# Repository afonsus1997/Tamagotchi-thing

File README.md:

# Tamagotchi Thing

Just a dumb attempt to make a tamagotch.

Based on the amazing work of [jcrona](https://github.com/jcrona)!

#### Credits

3D models:
 - Kailh buttons by Manh Le

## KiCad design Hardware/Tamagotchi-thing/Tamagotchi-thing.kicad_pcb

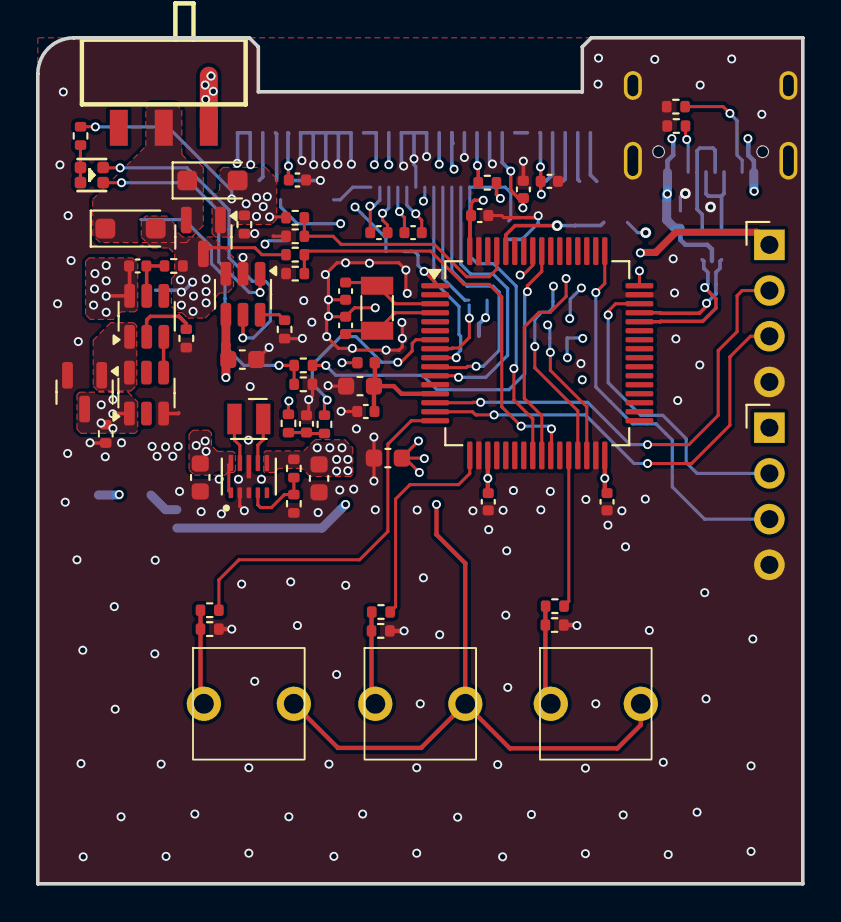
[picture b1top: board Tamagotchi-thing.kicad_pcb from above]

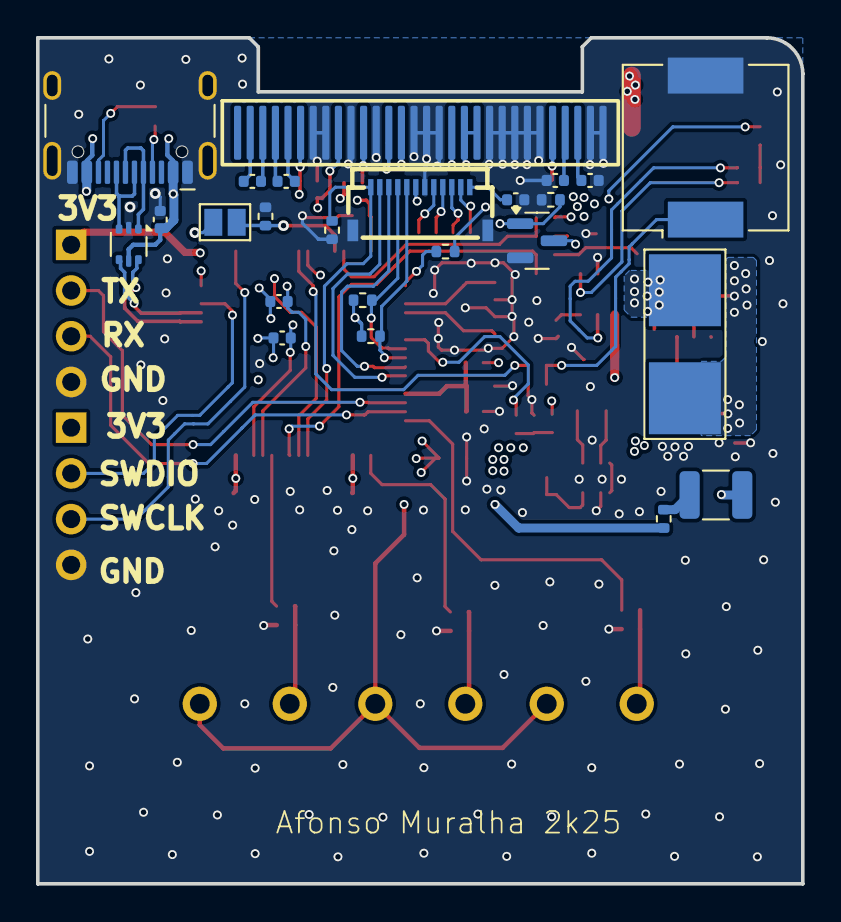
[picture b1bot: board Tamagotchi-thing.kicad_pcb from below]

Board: 4 copper layers, 42.5 x 47.0 mm, 86 parts (24 on the bottom side), 69 nets.

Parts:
BT1: Battery; Battery_Pads_4x4
C4, C5, C6: 1uF; C_0402_1005Metric
C7, C9, C10, C11, C12: 2.2uF; C_0402_1005Metric
C8: 4.7uF; C_0402_1005Metric
C13, C14: 12pF; C_0402_1005Metric
C15, C19, C20, C21, C24, C28: 100nF; C_0402_1005Metric
C18: 10nF; C_0603_1608Metric
C22: 1uF; C_0603_1608Metric
C23: 10nF; C_0402_1005Metric
C25, C27: 10uF; C_0603_1608Metric
C26: 22uF; C_0603_1608Metric
D1, D2: D_Schottky; D_SOD-123F
D3: LED_Dual_KKA; LED-SMD_4P-L1.6-W1.5-TL-1
J1: Conn_01x14; R_1210_3225Metric
J3: Conn_01x30; FFC-SMD_12P-P0.50_FH34SRJ-12S-0.5SH
J5: Conn_01x30; sh1106-1.3inch-oled_1
J6: USB_C_Receptacle_USB2.0; USB_C_Receptacle_HCTL_HC-TYPE-C-16P-01A
J7, J8: Conn_01x04; PinHeader_1x04_P2.54mm_Horizontal
JP1: SolderJumper_2_Open; SolderJumper-2_P1.3mm_Open_Pad1.0x1.5mm
L1: 39nH; L_0402_1005Metric
L2: 0.47uH; L_Wurth_WE-LQSH-2010
LS1: Speaker_Crystal; Buzzer_CUI_CPT-9019S-SMT
Q1: BSS138; SOT-23
Q3, Q4: AO3401A; SOT-23
Q5: FS8205A; SOT-23-6
R1: 15; R_0402_1005Metric
R2, R3, R4: 10k; R_0402_1005Metric
R6, R7, R11, R15, R16, R17, R18, R19, R22, R28, R32, R33: 100k; R_0402_1005Metric
R8, R9: 4.7k; C_0402_1005Metric
R10: 390k; C_0402_1005Metric
R12, R21, R27, R31: 330; R_0402_1005Metric
R13, R14: 5.1k; R_0402_1005Metric
R20, R34: 0; R_0402_1005Metric
R25, R35: 100; R_0402_1005Metric
R26, R36: 1k; R_0402_1005Metric
R37: 511k; R_0402_1005Metric
R38: 91k; R_0402_1005Metric
R39: 2k; R_0402_1005Metric
R42: 1.6k; R_0402_1005Metric
SW2, SW4, SW5: SW_Push; Kailh_mouse_button
SW6: SW_SPDT_321; SW-SMD_SK-3245S-L1-A-1
U1: USBLC6-2P6; SOT-666
U2: STM32L073RBTx; LQFP-64_10x10mm_P0.5mm
U3: DW01A; SOT-23-6
U4: TPS63802DLAR; VREG_TPS63802DLAR
U5: TP4057; TSOT-23-6
Y1: 32768Hz - 12,5 pF; Crystal_SMD_3215-2Pin_3.2x1.5mm

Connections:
3V3: C7.2, C10.2, C18.1, C19.1, C20.1, C21.1, C26.1, J3.7, J5.6, J5.9, J5.13, J7.1, J8.1, JP1.1 (A), L1.1, R1.2, R3.1, R4.1, R7.2, R8.2, R9.2, R11.1, R20.1, R37.1, SW2.2, SW4.2, SW5.2, U2.19 (VDD), U2.32 (VDD), U2.48 (VDD_USB), U2.64 (VDD), U4.6 (VOUT)
3V3A: C22.1, C23.1, L1.2, U2.13 (VDDA)
/MCU/BOOT0: JP1.2 (B), R15.1, U2.60 (BOOT0)
/MCU/LCD2.SCL: J3.9, R4.2, U2.8 (I2C3_SCL)
/MCU/LCD2.SDA: J3.8, R3.2, U2.9 (I2C3_SDA)
/MCU/LCD2_A0: J3.10, U2.10 (PC2)
/MCU/LCD2_BL_EN: Q1.1 (G), R2.1, U2.57 (TIM3_CH2)
/MCU/LCD2_CS: J3.12, R6.1, U2.24 (PC4)
/MCU/LCD2_RES: J3.11, U2.11 (PC3)
/MCU/OLED.SCL: J5.18, R8.1, U2.29 (I2C2_SCL)
/MCU/OLED.SDA: J5.19, J5.20, R9.1, U2.30 (I2C2_SDA)
/MCU/OLED_RST: J5.14, U2.25 (PC5)
/MCU/OSC_32_IN: C13.1, U2.3 (RCC_OSC32_IN), Y1.1
/MCU/OSC_32_OUT: C14.1, U2.4 (RCC_OSC32_OUT), Y1.2
/MCU/RST: R12.2, U2.7 (NRST)
/MCU/SPK: R25.2, U2.56 (TIM3_CH1)
/MCU/SWCLK: J7.3, U2.49 (SYS_SWCLK)
/MCU/SWDIO: J7.2, U2.46 (SYS_SWDIO)
/MCU/SW_CENTER: R27.1, U2.17 (PA3)
/MCU/SW_LEFT: R21.1, U2.16 (PA2)
/MCU/SW_RIGHT: R31.1, U2.28 (PB2)
/MCU/UART_RX: J8.3, U2.15 (USART4_RX)
/MCU/UART_TX: J8.2, U2.14 (USART4_TX)
/MCU/USB_D_N: U1.6 (I/O1), U2.44 (USB_DM)
/MCU/USB_D_P: U1.4 (I/O2), U2.45 (USB_DP)
/MCU/USB_D_RAW_N: J6.A7 (D-), J6.B7 (D-), U1.1 (I/O1)
/MCU/USB_D_RAW_P: J6.A6 (D+), J6.B6 (D+), U1.3 (I/O2)
/MCU/VBAT_SENSE: R18.2, R19.1, U2.26 (ADC_IN8)
/MCU/VBUS_SENSE: R16.2, R17.1, U2.61 (PB8)
/OLED/BS1: J5.11, R7.1
GND: C4.2, C7.1, C8.1, C10.1, C11.1, C13.2, C14.2, C15.2, C18.2, C19.2, C20.2, C21.2, C22.2, C23.2, C25.2, C26.2, C27.2, C28.2, J3.6, J3.MP (MountPin), J5.7, J5.8, J5.10, J5.12, J5.15, J5.16, J5.17, J5.21, J5.22, J5.23, J5.24, J5.25, J5.29, J5.30, J6.A1 (GND), J6.A12 (GND), J6.B1 (GND), J6.B12 (GND), J6.S1 (SHIELD), J7.4, J8.4, LS1.2, Q1.2 (S), Q4.2 (S), Q5.3 (S2), R2.2, R6.2, R10.1, R13.2, R14.2, R15.2, R17.2, R19.2, R22.2, R26.2, R28.2, R32.2, R33.2, R34.2, R36.2, R38.2, R42.2, U1.2 (GND), U2.12 (VSSA), U2.18 (VSS), U2.31 (VSS), U2.47 (VSS), U2.63 (VSS), U4.2 (MODE), U4.3 (AGND), U4.8 (GND), U5.2 (GND)
GND_BAT: BT1.2 (-), C24.2, Q4.3 (D), Q5.1 (D1), R34.1, U3.6 (GND)
unnamed: C15.1, R11.2, R12.1
unnamed: D1.1 (K), D2.1 (K), Q3.2 (S), SW6.2 (B)
unnamed: D3.3 (A2), D3.4 (A1), R39.2
unnamed: D3.1 (K1), U5.1 (~CHRG)
unnamed: D3.2 (K2), U5.5 (STDBY)
unnamed: J1.1, R1.1
unnamed: J1.2, Q1.3 (D)
unnamed: C4.1, J3.1
unnamed: C5.1, J3.2
unnamed: C5.2, J3.3
unnamed: C6.1, J3.4
unnamed: C6.2, J3.5
unnamed: C12.2, J5.2
unnamed: C12.1, J5.3
unnamed: C9.2, J5.4
unnamed: C9.1, J5.5
unnamed: J5.26, R10.2
unnamed: C8.2, J5.27
unnamed: C11.2, J5.28
unnamed: J6.A5 (CC1), R14.1
unnamed: J6.B5 (CC2), R13.1
unnamed: LS1.1, R25.1, R26.1
unnamed: Q4.1 (G), Q5.6 (G1), U3.1 (OD)
unnamed: Q5.4 (G2), U3.3 (OC)
unnamed: R21.2, R22.1, SW2.1
unnamed: R27.2, R28.1, SW4.1
unnamed: R31.2, R32.1, SW5.1
unnamed: C25.1, SW6.3 (A), U4.1 (EN), U4.10 (VIN)
unnamed: R20.2, U2.1 (VLCD)
unnamed: R36.1, U3.2 (CS)
unnamed: C24.1, R35.2, U3.5 (VCC)
unnamed: R37.2, R38.1, U4.4 (FB)
unnamed: L2.1, U4.9 (L1)
unnamed: L2.2, U4.7 (L2)
unnamed: R42.1, U5.6 (PROG)
VBAT: BT1.1 (+), D2.2 (A), Q3.3 (D), R18.1, R35.1, U5.3 (BAT)
VBUS: C27.1, C28.1, D1.2 (A), J6.A4 (VBUS), J6.A9 (VBUS), J6.B4 (VBUS), J6.B9 (VBUS), Q3.1 (G), R16.1, R33.1, R39.1, U1.5 (VBUS), U5.4 (V_{CC})

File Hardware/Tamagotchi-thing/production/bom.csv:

Reference,Qty,Value,LCSC,Voltage,DNP,Exclude from BOM,Exclude from Board,Footprint,Datasheet
C1,1,330nF,C5448882,25,DNP,,Excluded from board,Capacitor_SMD:C_0402_1005Metric,~
"C4,C5,C6",3,1uF,C29266,16V,,,,Capacitor_SMD:C_0402_1005Metric,~
C26,1,22uF,C59461,6.3,,,,Capacitor_SMD:C_0603_1608Metric,~
"C25,C27",2,10uF,C95839,6.3,,,,Capacitor_SMD:C_0603_1608Metric,~
Y1,1,"32768Hz - 12,5 pF",C32346,,,,,Crystal:Crystal_SMD_3215-2Pin_3.2x1.5mm,~
U5,1,TP4057,C725791,,,,,Package_TO_SOT_SMD:TSOT-23-6,http://toppwr.com/uploadfile/file/20230304/640302a47b738.pdf
U4,1,TPS63802DLAR,C2845237,,,,,TamagotchiThing:VREG_TPS63802DLAR,
U3,1,DW01A,C2927799,,,,,Package_TO_SOT_SMD:SOT-23-6,https://hmsemi.com/downfile/DW01A.PDF
U2,1,STM32L073RBTx,C2917159,,,,,Package_QFP:LQFP-64_10x10mm_P0.5mm,https://www.st.com/resource/en/datasheet/stm32l073rb.pdf
U1,1,USBLC6-2P6,C2827693,,,,,Package_TO_SOT_SMD:SOT-666,https://www.st.com/resource/en/datasheet/usblc6-2.pdf
SW6,1,SW_SPDT_321,C500049,,,,,TamagotchiThing:SW-SMD_SK-3245S-L1-A-1,~
R42,1,1.6k,C185451,,,,,Resistor_SMD:R_0402_1005Metric,~
R39,1,2k,C60488,,,,,Resistor_SMD:R_0402_1005Metric,~
R38,1,91k,C326721,,,,,Resistor_SMD:R_0402_1005Metric,~
R37,1,511k,C2684557,,,,,Resistor_SMD:R_0402_1005Metric,~
"R26,R36",2,1k,C106235,,,,,Resistor_SMD:R_0402_1005Metric,~
"R25,R35",2,100,C106232,,,,,Resistor_SMD:R_0402_1005Metric,~
"R20,R34",2,0,C106231,,DNP,,,Resistor_SMD:R_0402_1005Metric,~
"R13,R14",2,5.1k,C407575 ,,,,,Resistor_SMD:R_0402_1005Metric,~
"R12,R21,R27,R31",4,330,C105875,,,,,Resistor_SMD:R_0402_1005Metric,~
R11,1,100k,C25803,,,,,Resistor_SMD:R_0402_1005Metric,~
R10,1,390k,C163467,,,,,Capacitor_SMD:C_0402_1005Metric,~
"R8,R9",2,4.7k,C93943,,,,,Capacitor_SMD:C_0402_1005Metric,~
"R6,R7,R15,R16,R17,R18,R19,R22,R28,R32,R33",11,100k,C60491,,,,,Resistor_SMD:R_0402_1005Metric,~
R1,1,15,C105871,,,,,Resistor_SMD:R_0402_1005Metric,~
Q5,1,FS8205A,C2830320,,,,,Package_TO_SOT_SMD:SOT-23-6,https://www.diodes.com/assets/Datasheets/ds31770.pdf
"Q3,Q4",2,AO3401A,C15127,,DNP,,,Package_TO_SOT_SMD:SOT-23,~
LS1,1,Speaker_Crystal,C391035,,,,,Buzzer_Beeper:Buzzer_CUI_CPT-9019S-SMT,https://datasheet.lcsc.com/lcsc/1912111437_FUET-FUET-9018_C3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
L2,1,0.47uH,C89446,,,,,Inductor_SMD_Wurth:L_Wurth_WE-LQSH-2010,~
L1,1,39nH,C26443,,,,,Inductor_SMD:L_0402_1005Metric,~
J6,1,USB_C_Receptacle_USB2.0, C2894897,,,,,Connector_USB:USB_C_Receptacle_HCTL_HC-TYPE-C-16P-01A,https://www.usb.org/sites/default/files/documents/usb_type-c.zip
J3,1,Conn_01x30,C424659,,,,,TamagotchiThing:FFC-SMD_12P-P0.50_FH34SRJ-12S-0.5SH,~
D3,1,LED_Dual_KKA,C965839,,,,,TamagotchiThing:LED-SMD_4P-L1.6-W1.5-TL-1,~
C22,1,1uF,C15849,,,,,Capacitor_SMD:C_0603_1608Metric,~
C18,1,10nF,C15195,,,,,Capacitor_SMD:C_0603_1608Metric,~
"C15,C19,C20,C21,C24,C28",6,100nF,C2180552,,,,,Capacitor_SMD:C_0402_1005Metric,~
"C13,C14",2,12pF,C1547,,,,,Capacitor_SMD:C_0402_1005Metric,~
C8,1,4.7uF,C23733,,,,,Capacitor_SMD:C_0402_1005Metric,~

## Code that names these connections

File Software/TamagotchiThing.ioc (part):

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Mcu.Name=STM32L073R(B-Z)Tx
Mcu.Package=LQFP64
Mcu.UserName=STM32L073RBTx
PA0.Mode=Asynchronous
PA0.Signal=USART4_TX
PA1.Mode=Asynchronous
PA1.Signal=USART4_RX
PA11.Mode=Device
PA11.Signal=USB_DM
PA12.Mode=Device
PA12.Signal=USB_DP
PA13.Mode=Serial_Wire
PA13.Signal=SYS_SWDIO
PA14.Mode=Serial_Wire
PA14.Signal=SYS_SWCLK
PA2.GPIOParameters=GPIO_Label
PA2.GPIO_Label=SW_LEFT
PA2.Signal=GPIO_Input
PA3.GPIOParameters=GPIO_Label
PA3.GPIO_Label=SW_CENTER
PA3.Signal=GPIO_Input
PA4.Signal=SPI1_NSS
PA5.Mode=Full_Duplex_Master
PA5.Signal=SPI1_SCK
PA6.Mode=Full_Duplex_Master
PA6.Signal=SPI1_MISO
PA7.Mode=Full_Duplex_Master
PA7.Signal=SPI1_MOSI
PA8.GPIOParameters=GPIO_Label
PA8.GPIO_Label=LCD_DC
PA8.Signal=GPIO_Output
PB0.GPIOParameters=GPIO_Label
PB0.GPIO_Label=VBAT_SENSE
PB0.Mode=IN8
PB0.Signal=ADC_IN8
PB1.GPIOParameters=GPIO_Label
PB1.GPIO_Label=LCD_BL
PB1.Signal=S_TIM3_CH4
PB10.Mode=I2C
PB10.Signal=I2C2_SCL
PB11.Mode=I2C
PB11.Signal=I2C2_SDA
PB2.GPIOParameters=GPIO_Label
PB2.GPIO_Label=SW_RIGHT
PB2.Signal=GPIO_Input
PB4.GPIOParameters=GPIO_Label
PB4.GPIO_Label=SPK
PB4.Signal=S_TIM3_CH1
PB5.GPIOParameters=GPIO_Label
PB5.GPIO_Label=LCD2_BL
PB5.Signal=S_TIM3_CH2
PB8.GPIOParameters=GPIO_Label
PB8.GPIO_Label=VBUS_SENSE
PB8.Signal=GPIO_Input
PC0.Mode=I2C
PC0.Signal=I2C3_SCL
PC1.Mode=I2C
PC1.Signal=I2C3_SDA
PC13.Mode=Timestamp enabled
PC13.Signal=RTC_TS
PC14-OSC32_IN.Mode=LSE-External-Oscillator
PC14-OSC32_IN.Signal=RCC_OSC32_IN
PC15-OSC32_OUT.Mode=LSE-External-Oscillator
PC15-OSC32_OUT.Signal=RCC_OSC32_OUT
PC2.GPIOParameters=GPIO_Label
PC2.GPIO_Label=LCD2_A0
PC2.Signal=GPIO_Output
PC3.GPIOParameters=GPIO_Label
PC3.GPIO_Label=LCD2_RES
PC3.Signal=GPIO_Output
PC4.GPIOParameters=GPIO_Label
PC4.GPIO_Label=LCD2_CS
PC4.Signal=GPIO_Output
PC5.GPIOParameters=GPIO_Label
PC5.GPIO_Label=OLED_RST
PC5.Signal=GPIO_Output
RCC.HSE_VALUE=8000000
RCC.SYSCLKFreq_VALUE=16000000
RCC.SYSCLKSource=RCC_SYSCLKSOURCE_HSI
board=custom

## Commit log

2025-07-15 schematic work
2025-07-15 Schematic and layout work
2025-07-16 Schematic and Layout work. DRC cleanup
2025-07-16 Final touches. Exported production files
2025-07-16 Minor fixes. Added via stitching. BOM adjustments. Sent to production
2025-07-22 Started adding sw
2025-07-29 Replaced sw project with cmake project
2025-07-30 trying to port u8g2
2025-07-30 u8g2 working
2025-07-30 updated u8g2, changed i2c speed to 400kHz
2025-07-30 u8g2 menu works. started adding uiserio stuff
2025-07-30 organization and button userui stuff
2025-07-31 started working on usb
2025-07-31 usb cdc working
2025-07-31 started working on internal fs
2025-08-01 ui management
2025-08-01 menu ui
2025-08-01 forms and buttons
2025-08-01 RTC working
2025-08-01 added logging
2025-08-01 started adding tama stuff
2025-08-02 fixed buttons
2025-08-02 minor form fixes
2025-08-02 minor changes
2025-08-03 tama_lib work
2025-08-03 more tamalib work
2025-08-03 minor fix
2025-08-03 tama debugging
2025-08-03 i can see an egg on screen
2025-08-03 New linker script
2025-08-03 more linker script stuff
2025-08-03 faster not, still not quite right
2025-08-04 trying to move to lptim
2025-08-05 returned to tim6
2025-08-05 timing is good now
2025-08-05 updated ld
2025-08-05 changed to 1Mhz
2025-08-05 524288
2025-08-06 Added button handling to emulation
